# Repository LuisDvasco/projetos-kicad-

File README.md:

# projetos-kicad-
Primeiros projetos na plataforma kicad

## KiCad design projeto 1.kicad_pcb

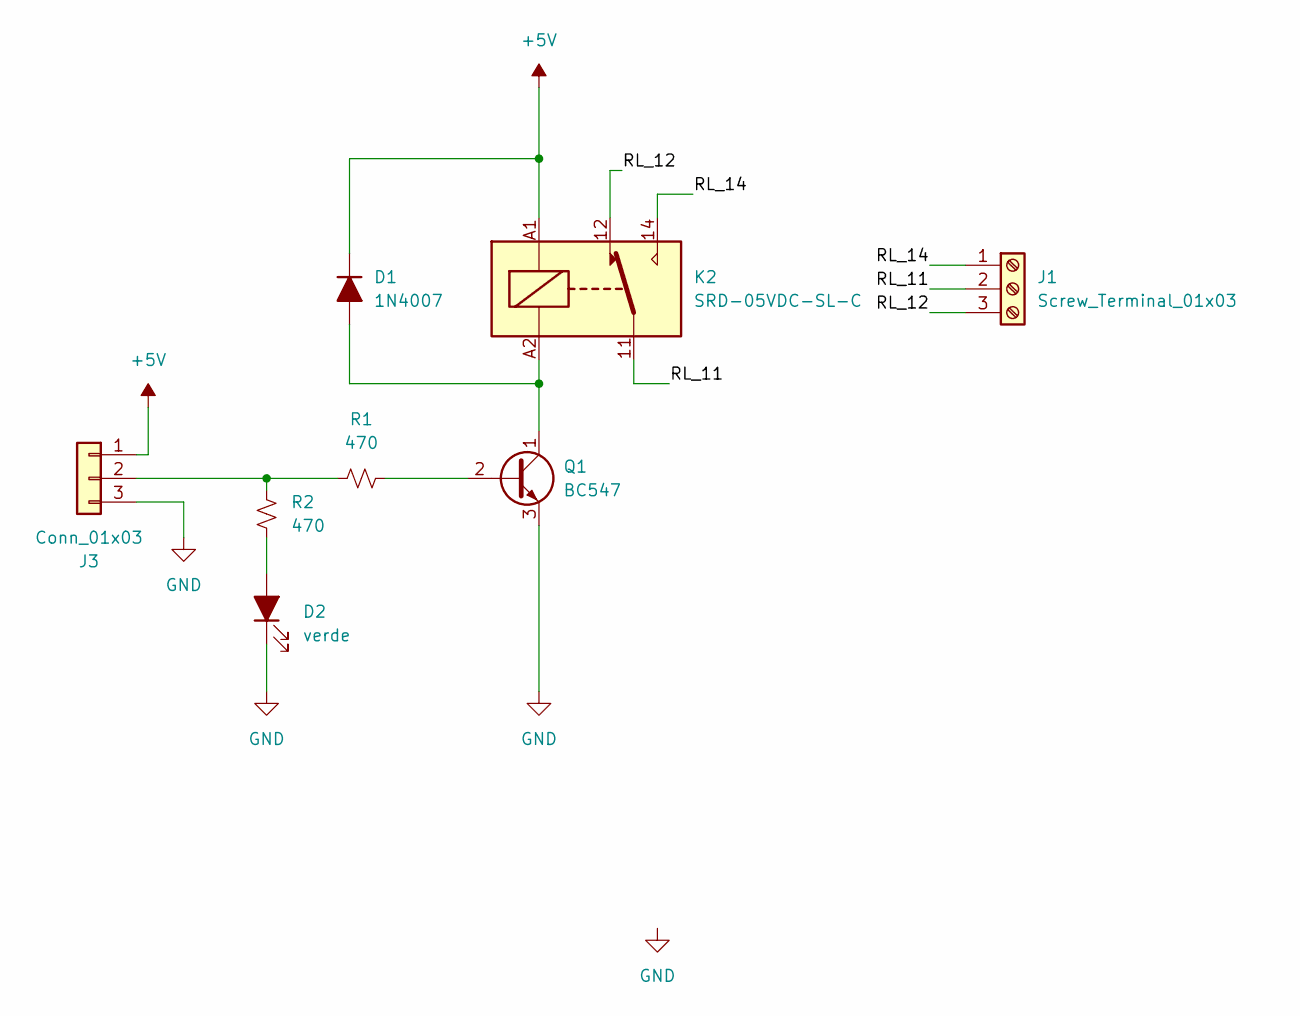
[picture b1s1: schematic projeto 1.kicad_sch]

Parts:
D1: 1N4007; D_DO-41_SOD81_P10.16mm_Horizontal
D2: verde; LED_D5.0mm
J1: Screw_Terminal_01x03; TerminalBlock_Phoenix_MKDS-3-3-5.08_1x03_P5.08mm_Horizontal
J3: Conn_01x03; PinHeader_1x03_P2.54mm_Vertical
K2: SRD-05VDC-SL-C; Relay_SPDT_Finder_36.11
Q1: BC547; TO-92_Inline
R1, R2: 470; R_Axial_DIN0207_L6.3mm_D2.5mm_P7.62mm_Horizontal

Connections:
+5V: D1.1 (K), J3.1, K2.A1
/RL_11: J1.2, K2.11
/RL_12: J1.3, K2.12
/RL_14: J1.1, K2.14
GND: D2.1 (K), J3.3, Q1.3 (E)
unnamed: D1.2 (A), K2.A2, Q1.1 (C)
unnamed: D2.2 (A), R2.2
unnamed: J3.2, R1.2, R2.1
unnamed: Q1.2 (B), R1.1

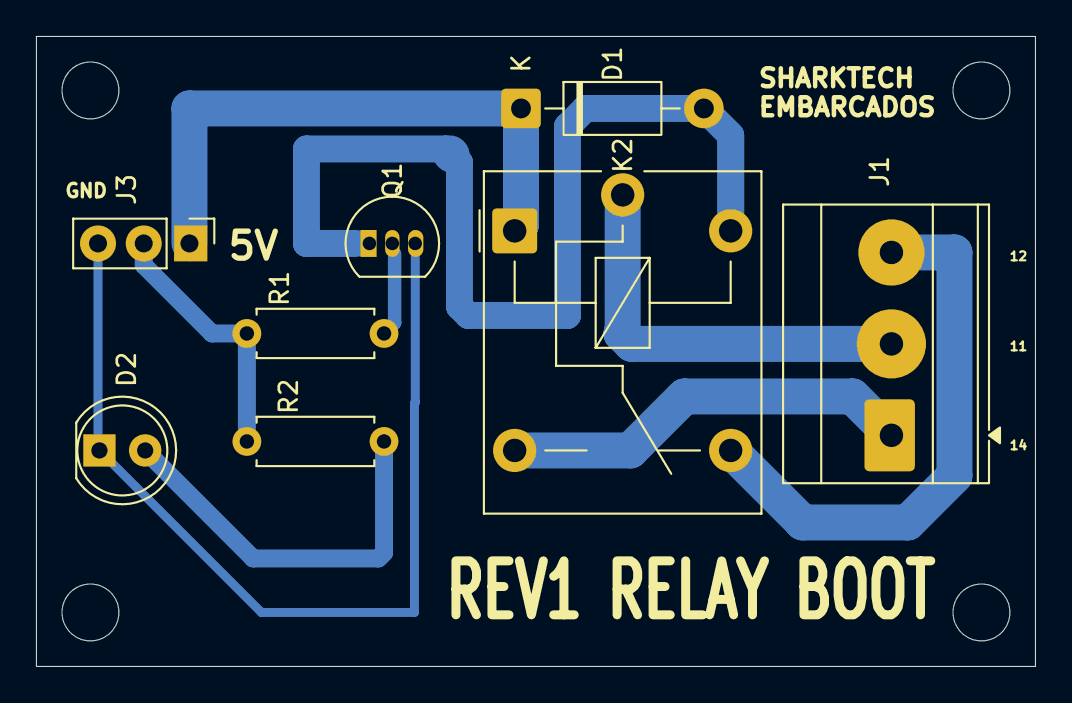
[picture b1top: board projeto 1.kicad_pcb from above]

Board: 2 copper layers, 55.5 x 35.0 mm, 8 parts (0 on the bottom side), 9 nets.

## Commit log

2026-01-07 Add files via upload
    Pcb rele control
